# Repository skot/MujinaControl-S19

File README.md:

# MujinaControl-S19

An open-hardware Antminer S19 controlboard built around the Rockchip RV1106G2, for [Mujina](https://mujina.org) mining firmware. It keeps the bitcrane v3.1 form factor, outline, mounting holes and miner connectors, and replaces bitcrane's RP2040 with a Linux-capable SoC, Ethernet and local storage.

**Status (2026-11-12):** schematic complete, PCB placed and fully routed on six layers. ERC 0; DRC 0 violations, 0 unconnected items, 0 schematic-parity issues. Every purchased part has a fab (LCSC) part number. **Not yet reviewed for manufacturing and not built or tested.** Do not order until the review below is done.

Open `MujinaControl-S19.kicad_pro` with **KiCad 10.99 or later**. The files use a newer format than KiCad 10.0 can read.

## Hardware

- **SoC:** RV1106G2 with 128 MB in-package DDR3L, 24 MHz crystal and RTC crystal.
- **Storage:** W25N02KVZEIR 2 Gbit (256 MB) SPI NAND on the quad-SPI bus, following the Luckfox Pico Pro/Max, plus a microSD socket. A bootable NAND takes precedence over microSD.
- **Network and USB:** 100BASE-TX through the SoC's internal PHY and an integrated MagJack. USB-C device port for recovery and console; VBUS is detection-only, so **12 V must be present for USB recovery**.
- **Power:** 12 V from J1's 6-pin input (pins 1–3 positive, 4–6 ground) through reverse-polarity P-MOSFET Q1 (NTTFS008P03P8Z) and an SMBJ15A TVS. There is no controller fuse. Six TPS62933 bucks: 12 V → 5 V system (2 A budget), then sequenced 0.9 V core, 0.9 V CPU, 1.35 V DDR, 1.8 V and 3.3 V. Five TPS3808 supervisors (trip at about 90 % of each rail) qualify the sequence and hold reset.
- **Hashboards:** three ports, each with its own hardware UART, sharing one hashboard I²C bus; BCB100-style I²C/UART pull-ups and plug-detect pull-downs, and a TPS22919 switched 3.3 V supply per port, enabled directly by SoC GPIOs.
- **Fans:** four independent channels, PWM and tach, each sized for 3 A; the input stage carries all four fans plus the board. Each channel has both a 1×4 2.54 mm and a 2×2 4.2 mm footprint; fit one. Two 100 µF bulk capacitors on the fan rail.
- **PSU and accessories:** PSU I²C and enable, accessory header J15 (display I²C, GPIO, 5 V / 3.3 V), console UART on J16 (pin 1 TX, 2 GND, 3 RX, 3.3 V), RESET and BOOT (maskrom) right-angle buttons beside the Ethernet jack.

J1–J14 keep bitcrane's pin assignments. The SoC pin allocation is in `docs/pin-allocation.md`.

## Schematic

Ten sheets: system overview, SoC interfaces, sequenced regulators, power qualification, SoC supply and bypass, boot storage and clocks, Ethernet and USB, hashboard interfaces, fan interfaces, input power and service. Cross-sheet signals use global labels; resistors use US-style symbols.

## PCB

- 110 × 100 mm, six layers, nominal 1.6 mm FR-4, ENIG, 1 oz outer / 0.5 oz inner, using the fab's JLC06161H-3313 stackup (`docs/pcb-stackup.md`).
- Layers: F.Cu signals and parts; In1 ground; In2 3.3 V plane with islands for core, DDR, 1.8 V, 5 V and 12 V; In3 slow signals; In4 ground; B.Cu signals.
- 310 footprints, 1925 tracks, 774 vias. All vias are 0.45 mm diameter / 0.30 mm drill; minimum track 0.127 mm (SoC escapes and Ethernet pairs).
- USB, Ethernet, SD card and SPI NAND are length-matched within the RV1106 hardware-guide limits.
- Each regulator follows the TPS62933 datasheet layout, with its own stitched ground pour. 414 ground vias in total; wherever a via is allowed, no point is more than 6 mm from one.
- Reference designators are hidden on the silkscreen; the printed artwork is the RESET and BOOT labels and the Mujina badger logo.

Routing details, measurements and history are in `docs/routing-current.md`. The other routing documents describe the board before the 2026-11-10 rip-up.

## Assembly and parts

The board is meant to be assembled by the fab. Every purchased part carries `LCSC` and `MPN` fields: 65 part numbers, 24 basic, 9 preferred and 32 extended, checked against live stock on 2026-11-12. The RV1106G2 needs the fab's standard (not economic) assembly. Stock was low for Q1 and the hashboard connectors J3–J5. See `docs/bom-fab-stock.md`. Fab settings are in `MujinaControl-S19.fab.json` (`order: false`).

## Before ordering

1. **Manufacturing review.** The routing was largely laid by a grid search: it is rule-clean but not tidy. The east-side hashboard lines are long (up to 117 mm) with up to 9 vias. They are slow signals, but they should be reviewed and could be shortened.
2. **Hashboard and PSU compatibility.** Confirm the real S19 hashboard and PSU voltages, reset and plug-detect polarity, PSU-enable polarity and powered/unpowered behaviour. Matching bitcrane's connections is not a measured compatibility test.
3. **Power.** Check cold start, slow ramp, brownout and shutdown on all rails, the supervisor thresholds, and regulator transient response. Measure Q1 and the 12 V copper at the full four-fan load. Upstream wiring must protect against shorts, as there is no controller fuse.
4. **Footprints and parts.** Audit the footprints against datasheets, especially the SoC and NAND exposed pads, MagJack, crystals, inductors and microSD. Re-check stock before ordering.
5. **Firmware.** Bring up the UART, PWM and I²C pin groups, fan tach, hashboard power GPIOs, NAND boot and USB recovery in the BSP. Keep the CPU at its fixed 0.9 V operating point.
6. **On hardware.** Tune the crystals; check USB and Ethernet signal integrity, ESD, thermals and EMC.

## Files

- `MujinaControl-S19.kicad_pro` with ten `.kicad_sch` sheets, `.kicad_pcb` and `.kicad_dru` (custom rules).
- `lib/`, `models/`, `3d/`: project-local symbols, footprints and 3D models.
- `docs/`: design notes for each change (stackup, placement, regulators, routing, parts).
- `scripts/`: the original generator `build_schematic.py`. **Do not rerun it**; it would overwrite the hand-edited schematic. `validate_design.py` and `verify_readability.py` are read-only checks.
- Check reports, renders and working evidence are kept outside this repository, in `build/MujinaControl-S19/` at the workspace root.

## Sources and attribution

- [Braiins BCB100](https://github.com/braiins/BCB100): open-source S19 control board (CERN-OHL-S v2), used as the reference for hashboard interface biasing and logic-power control (I2C/UART pull-ups, plug-detect pull-downs and per-port switched 3.3 V). Thanks to Braiins for publishing it.
- [bitcrane](https://github.com/skot/bitcrane) v3.1 (CERN-OHL v2): form factor, outline, mounting holes, connector pinouts and placements, fan-header options, and the inherited `bitaxe` and `bitcrane` libraries.
- Raven1106 v1.1: starting RV1106 package-pin definition, QFN footprint and model, and storage reference. Its full SBC circuit was not copied. No top-level licence was found for Raven; clarify reuse terms for the derived library assets before publishing them more widely.
- Luckfox Pico Pro/Max: SPI NAND reference.
- Rockchip RV1106 datasheet Rev 2.2 and hardware design guide: pin functions, power and layout rules.
- [TI TPS62933](https://www.ti.com/lit/ds/symlink/tps62933.pdf), [TI TPS3808](https://www.ti.com/lit/ds/symlink/tps3808.pdf), [TI TPS22919](https://www.ti.com/lit/ds/symlink/tps22919.pdf), [onsemi NTTFS008P03P8Z](https://www.onsemi.com/download/data-sheet/pdf/nttfs008p03p8z-d.pdf) and [Nexperia PESD3V3Y1BSF](https://assets.nexperia.com/documents/data-sheet/PESD3V3Y1BSF.pdf) datasheets.

Standard KiCad symbols and footprints are copied into the project-local libraries. Their original licence and attribution markings still apply.

## License

CERN Open Hardware Licence v2, Strongly Reciprocal (`LICENSE`).

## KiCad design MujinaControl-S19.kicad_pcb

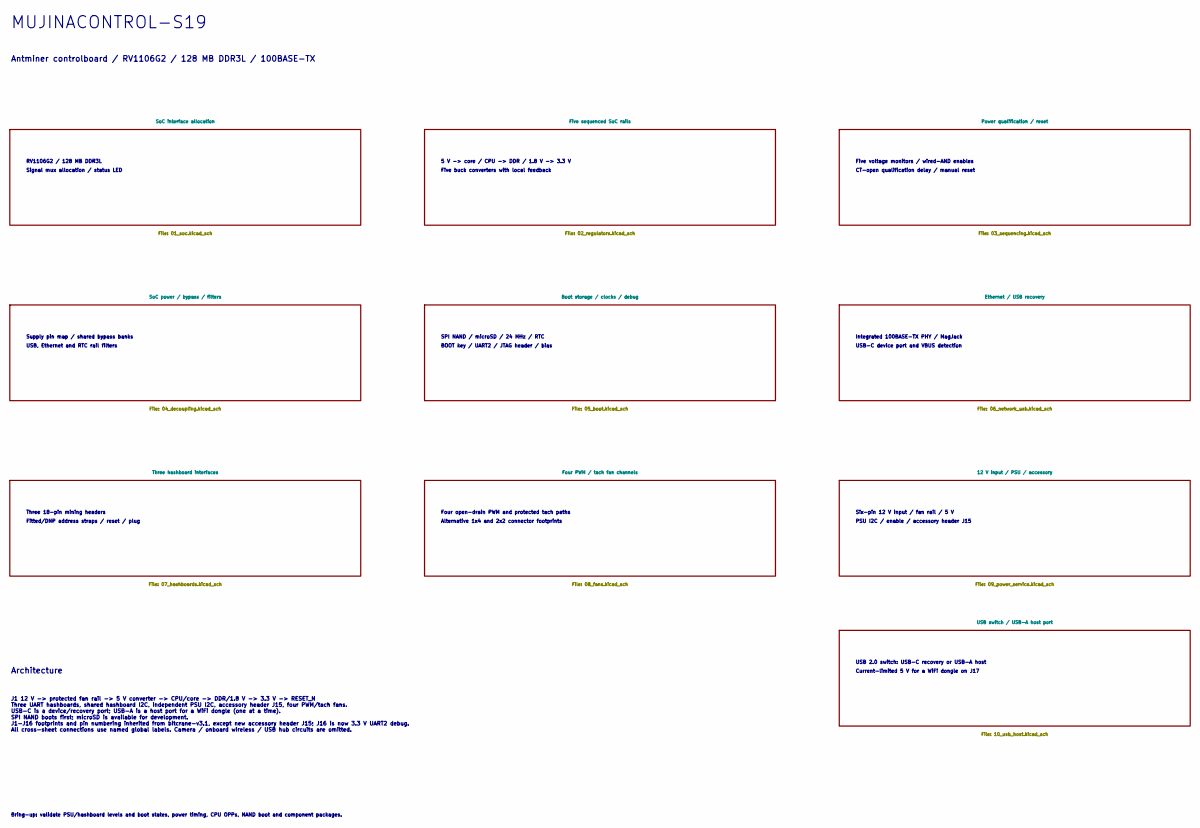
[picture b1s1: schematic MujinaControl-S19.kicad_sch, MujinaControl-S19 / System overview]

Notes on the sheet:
USB, Ethernet and RTC rail filters
Integrated 100BASE-TX PHY / MagJack
Five voltage monitors / wired-AND enables
PSU I2C / enable / accessory header J15
USB 2.0 switch: USB-C recovery or USB-A host
MUJINACONTROL-S19
5 V -> core / CPU -> DDR / 1.8 V -> 3.3 V
Architecture
Five buck converters with local feedback
BOOT key / UART2 / JTAG header / bias
Alternative 1x4 and 2x2 connector footprints
USB-C device port and VBUS detection
SPI NAND / microSD / 24 MHz / RTC
J1 12 V -> protected fan rail -> 5 V converter -> CPU/core -> DDR/1.8 V -> 3.3 V -> RESET_N Three UART hashboards, shared hashboard I2C, independent PSU I2C, accessory header J15, four PWM/tach fans. USB-C is a device/recovery port; USB-A is a host port for a WiFi dongle (one at a time).
SPI NAND boots first; microSD is available for development. J1-J16 footprints and pin numbering inherited from bitcrane-v3.1, except new accessory header J15; J16 is now 3.3 V UART2 debug. All cross-sheet connections use named global labels. Camera / onboard wireless / USB hub circuits are omitted.
Supply pin map / shared bypass banks
Antminer controlboard / RV1106G2 / 128 MB DDR3L / 100BASE-TX
CT-open qualification delay / manual reset
Fitted/DNP address straps / reset / plug
RV1106G2 / 128 MB DDR3L
Current-limited 5 V for a WiFi dongle on J17
Bring-up: validate PSU/hashboard levels and boot states, power timing, CPU OPPs, NAND boot and component packages.
Signal mux allocation / status LED
Three 18-pin mining headers
Four open-drain PWM and protected tach paths
Six-pin 12 V input / fan rail / 5 V

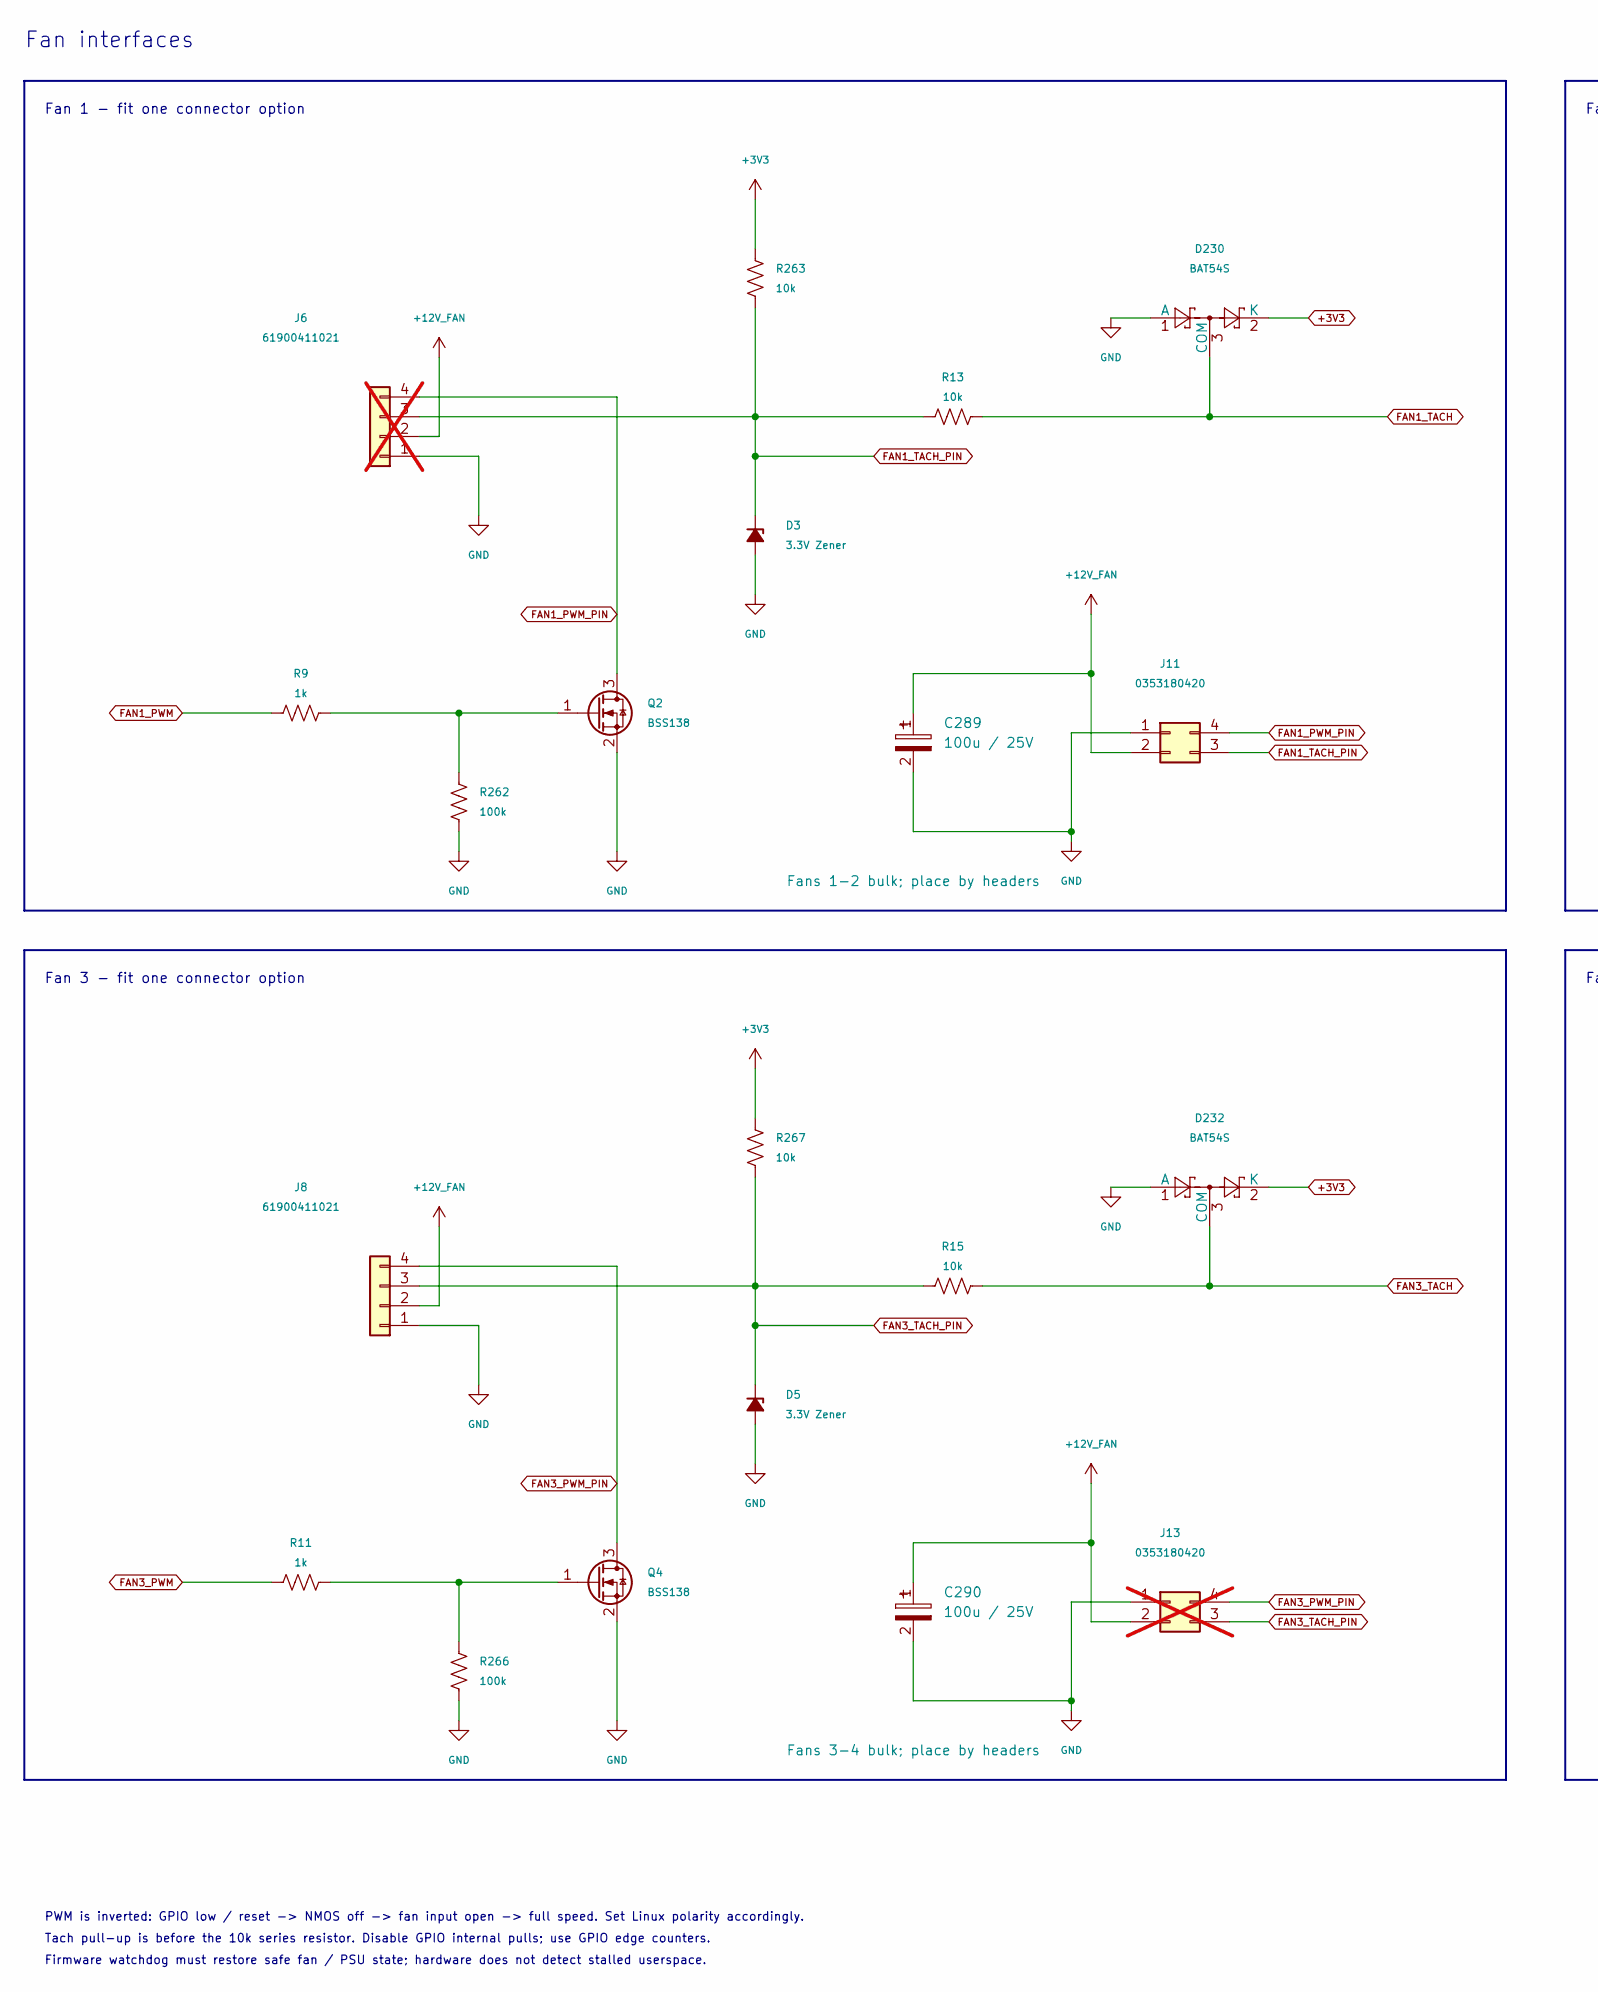
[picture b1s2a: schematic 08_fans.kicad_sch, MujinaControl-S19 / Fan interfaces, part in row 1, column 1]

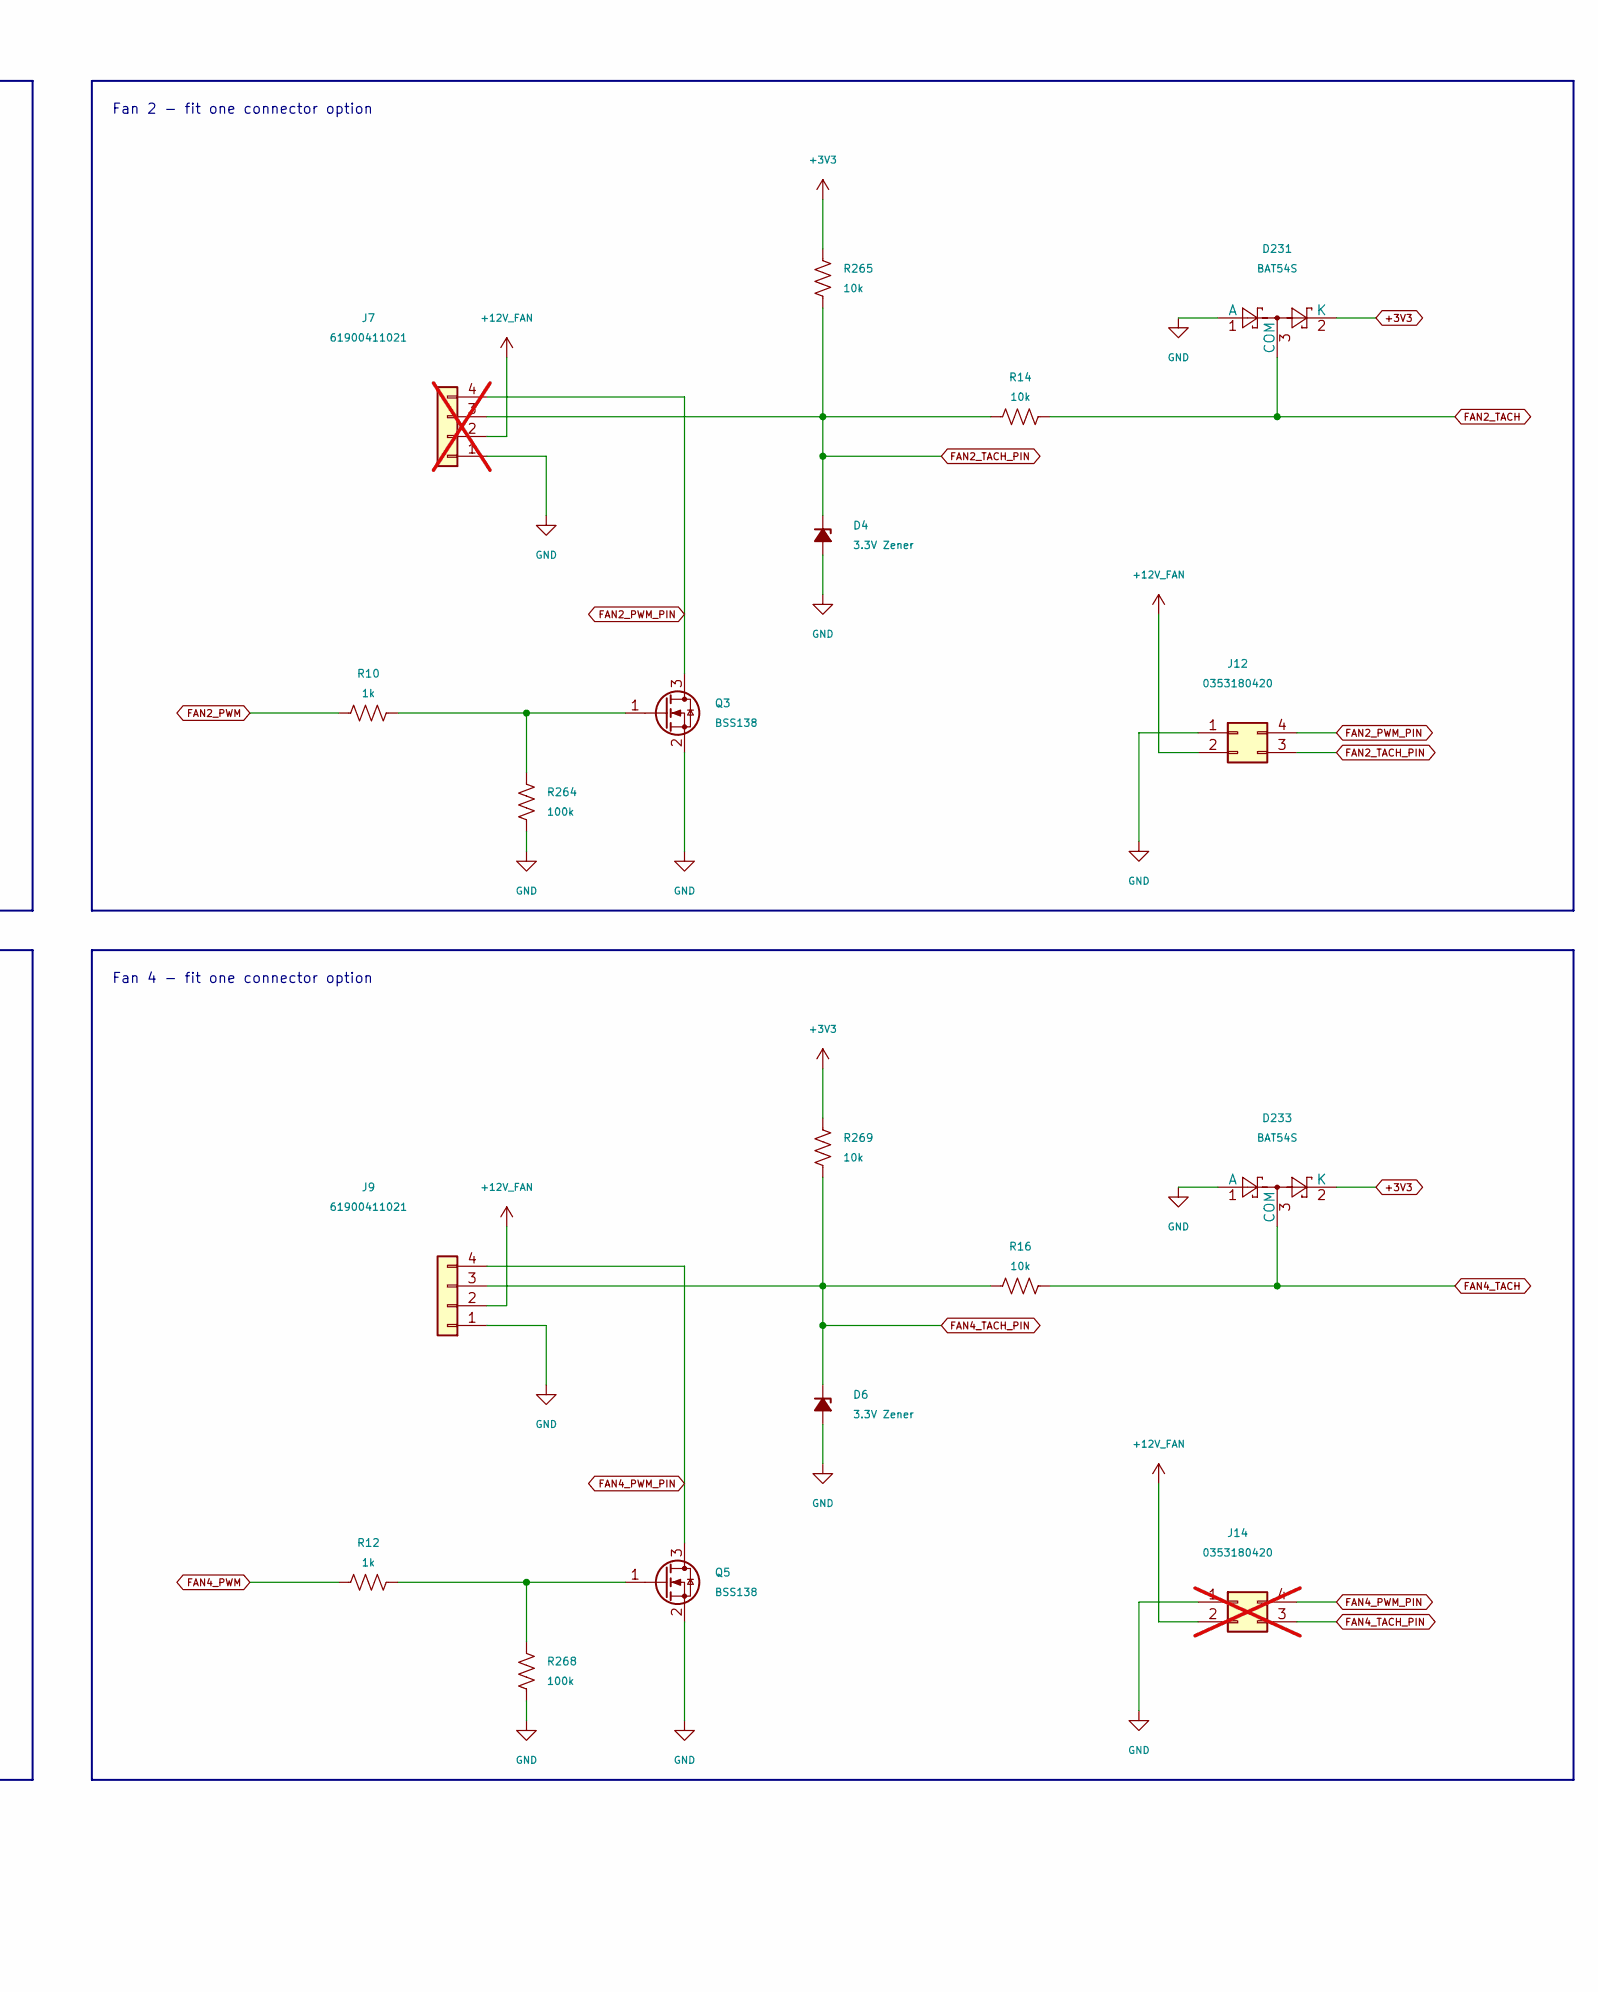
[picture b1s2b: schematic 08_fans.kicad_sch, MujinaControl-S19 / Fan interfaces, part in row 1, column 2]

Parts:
C289, C290: 100u / 25V; CP_Elec_6.3x7.7; MPN EEHZC1E101XP; LCSC C178640
D3, D4, D5, D6: 3.3V Zener; D_SOD-123; MPN BZT52C3V3; LCSC C19077396
D230, D231, D232, D233: BAT54S; SOT-23; MPN BAT54S; LCSC C7420333
J6, J7: 61900411021; CONN-TH_4P-P2.54_HCTL_HC-2510-4AW; MPN HC-2510-4AW; LCSC C2982043; not fitted
J8, J9: 61900411021; CONN-TH_4P-P2.54_HCTL_HC-2510-4AW; MPN HC-2510-4AW; LCSC C2982043
J11, J12: 0353180420; CONN-TH_4P-P4.20_5557-2X2AW; MPN 4.2-2*2AW; LCSC C54909
J13, J14: 0353180420; CONN-TH_4P-P4.20_5557-2X2AW; MPN 4.2-2*2AW; LCSC C54909; not fitted
Q2, Q3, Q4, Q5: BSS138; SOT-23; MPN BSS138; LCSC C7420339
R9, R10, R11, R12: 1k; R_0402_1005Metric; MPN 0402WGF1001TCE; LCSC C11702
R13, R14, R15, R16, R263, R265, R267, R269: 10k; R_0402_1005Metric; MPN 0402WGF1002TCE; LCSC C25744
R262, R264, R266, R268: 100k; R_0402_1005Metric; MPN 0402WGF1003TCE; LCSC C25741

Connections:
+3V3: D230.2 (K), D231.2 (K), D232.2 (K), D233.2 (K), R263.1, R265.1, R267.1, R269.1; also elsewhere on the board
+12V_FAN: C289.1, C290.1, J6.2, J7.2, J8.2, J9.2, J11.2, J12.2, J13.2, J14.2; also elsewhere on the board
FAN1_PWM: R9.1; also elsewhere on the board
FAN1_PWM_PIN: J6.4, J11.4, Q2.3 (D)
FAN1_TACH: D230.3 (COM), R13.2; also elsewhere on the board
FAN1_TACH_PIN: D3.1 (K), J6.3, J11.3, R13.1, R263.2
FAN2_PWM: R10.1; also elsewhere on the board
FAN2_PWM_PIN: J7.4, J12.4, Q3.3 (D)
FAN2_TACH: D231.3 (COM), R14.2; also elsewhere on the board
FAN2_TACH_PIN: D4.1 (K), J7.3, J12.3, R14.1, R265.2
FAN3_PWM: R11.1; also elsewhere on the board
FAN3_PWM_PIN: J8.4, J13.4, Q4.3 (D)
FAN3_TACH: D232.3 (COM), R15.2; also elsewhere on the board
FAN3_TACH_PIN: D5.1 (K), J8.3, J13.3, R15.1, R267.2
FAN4_PWM: R12.1; also elsewhere on the board
FAN4_PWM_PIN: J9.4, J14.4, Q5.3 (D)
FAN4_TACH: D233.3 (COM), R16.2; also elsewhere on the board
FAN4_TACH_PIN: D6.1 (K), J9.3, J14.3, R16.1, R269.2
GND: C289.2, C290.2, D3.2 (A), D4.2 (A), D5.2 (A), D6.2 (A), D230.1 (A), D231.1 (A), D232.1 (A), D233.1 (A), J6.1, J7.1, J8.1, J9.1, J11.1, J12.1, J13.1, J14.1, Q2.2 (S), Q3.2 (S), Q4.2 (S), Q5.2 (S), R262.2, R264.2, R266.2, R268.2; also elsewhere on the board
unnamed: Q2.1 (G), R9.2, R262.1
unnamed: Q3.1 (G), R10.2, R264.1
unnamed: Q4.1 (G), R11.2, R266.1
unnamed: Q5.1 (G), R12.2, R268.1

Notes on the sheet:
Fan 4 - fit one connector option
Tach pull-up is before the 10k series resistor. Disable GPIO internal pulls; use GPIO edge counters.
Firmware watchdog must restore safe fan / PSU state; hardware does not detect stalled userspace.
Fan interfaces
PWM is inverted: GPIO low / reset -> NMOS off -> fan input open -> full speed. Set Linux polarity accordingly.
Fan 2 - fit one connector option
Fan 1 - fit one connector option
Fan 3 - fit one connector option

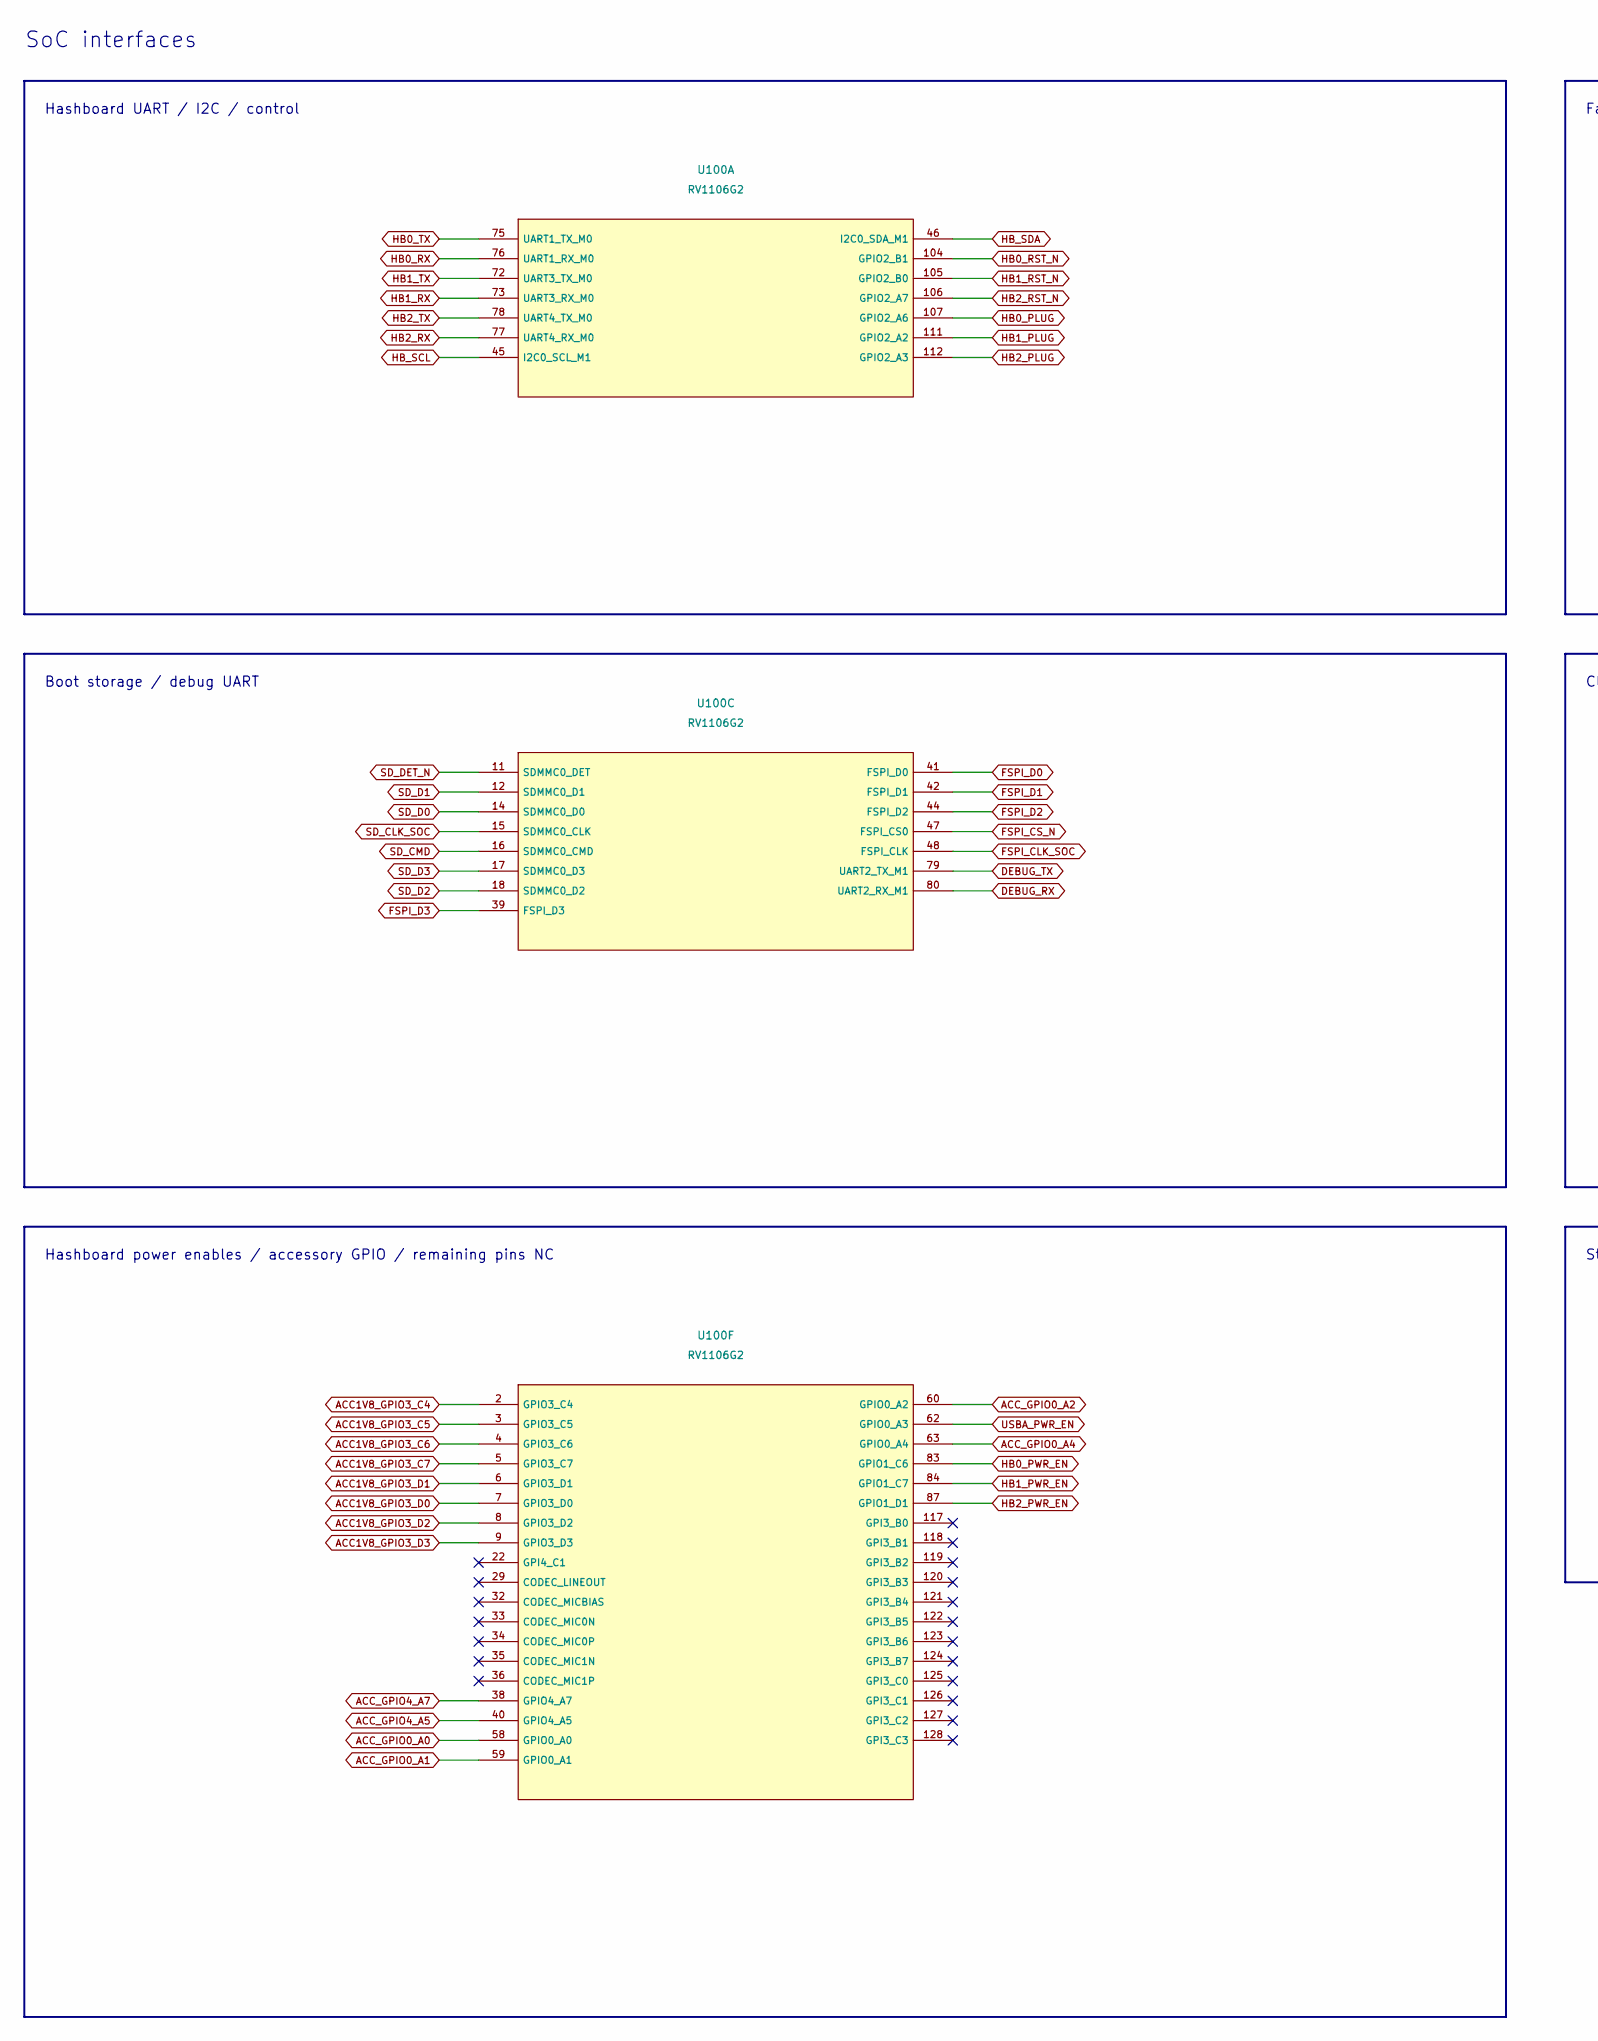
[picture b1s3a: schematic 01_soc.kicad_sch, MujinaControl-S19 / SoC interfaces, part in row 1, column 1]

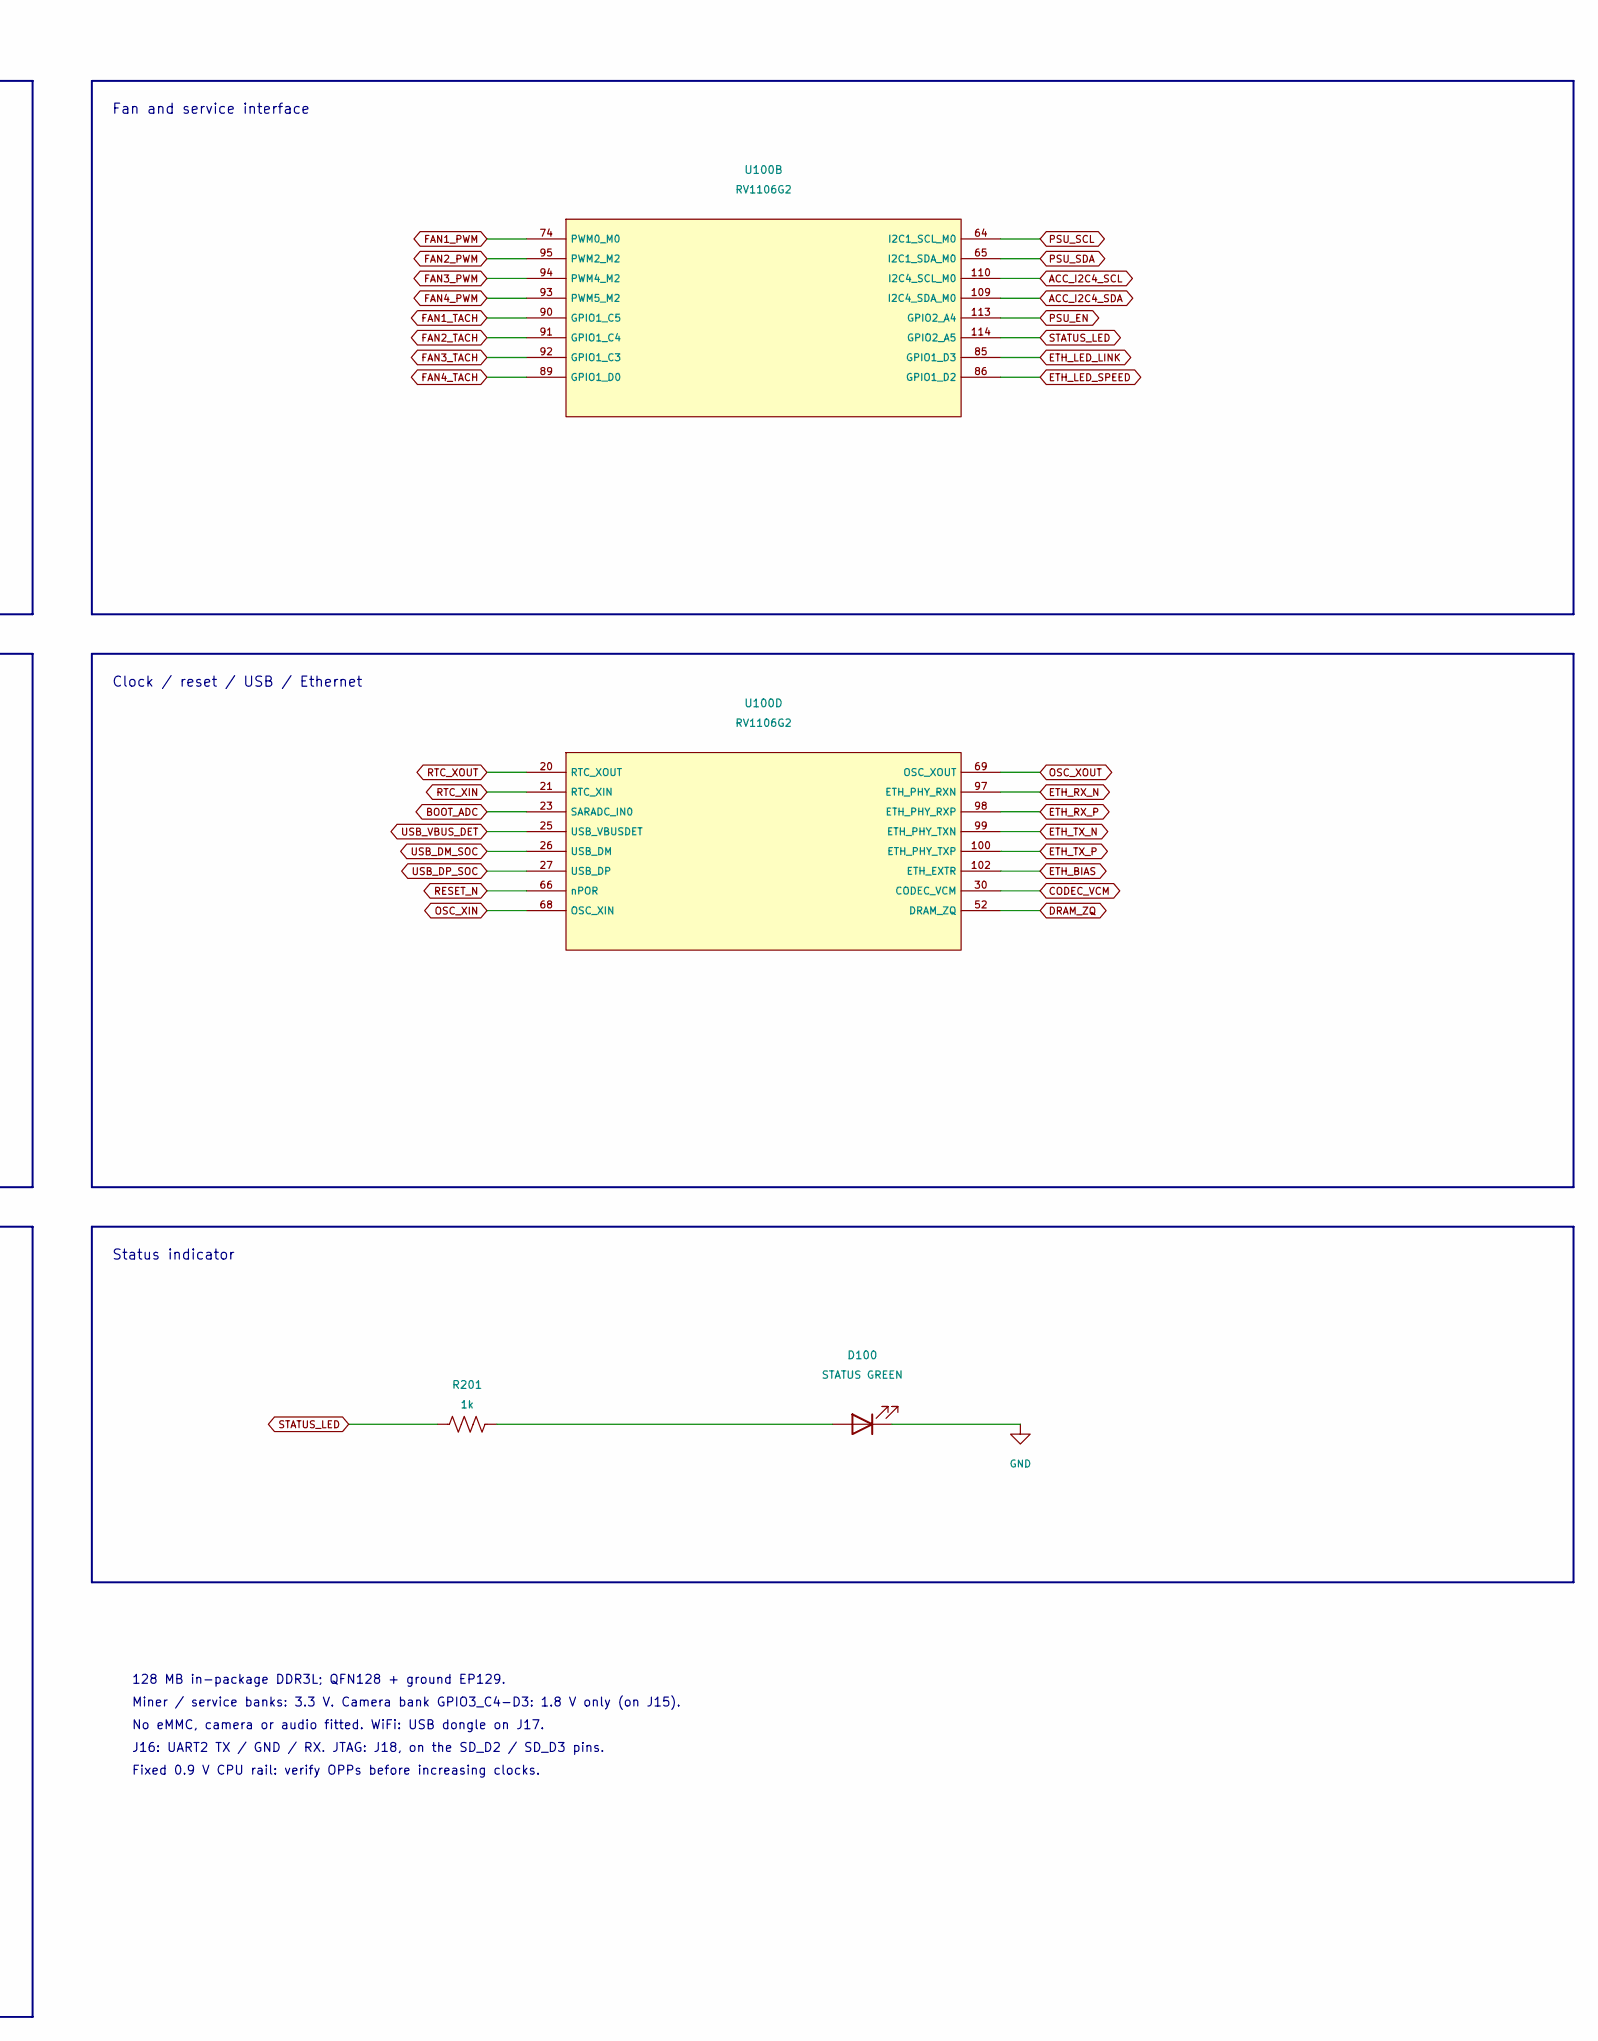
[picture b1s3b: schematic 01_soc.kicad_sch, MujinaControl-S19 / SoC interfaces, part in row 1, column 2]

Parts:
D100: STATUS GREEN; LED_0603_1608Metric; MPN LTST-C190KGKT; LCSC C125094
R201: 1k; R_0402_1005Metric; MPN 0402WGF1001TCE; LCSC C11702
U100: RV1106G2; Rockchip_QFN-128-1EP_12.3x12.3mm_P0.35mm_EP7x7mm; MPN RV1106G2; LCSC C5272606

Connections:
ACC1V8_GPIO3_C4: U100.2 (GPIO3_C4); also elsewhere on the board
ACC1V8_GPIO3_C5: U100.3 (GPIO3_C5); also elsewhere on the board
ACC1V8_GPIO3_C6: U100.4 (GPIO3_C6); also elsewhere on the board
ACC1V8_GPIO3_C7: U100.5 (GPIO3_C7); also elsewhere on the board
ACC1V8_GPIO3_D0: U100.7 (GPIO3_D0); also elsewhere on the board
ACC1V8_GPIO3_D1: U100.6 (GPIO3_D1); also elsewhere on the board
ACC1V8_GPIO3_D2: U100.8 (GPIO3_D2); also elsewhere on the board
ACC1V8_GPIO3_D3: U100.9 (GPIO3_D3); also elsewhere on the board
ACC_GPIO0_A0: U100.58 (GPIO0_A0); also elsewhere on the board
ACC_GPIO0_A1: U100.59 (GPIO0_A1); also elsewhere on the board
ACC_GPIO0_A2: U100.60 (GPIO0_A2); also elsewhere on the board
ACC_GPIO0_A4: U100.63 (GPIO0_A4); also elsewhere on the board
ACC_GPIO4_A5: U100.40 (GPIO4_A5); also elsewhere on the board
ACC_GPIO4_A7: U100.38 (GPIO4_A7); also elsewhere on the board
ACC_I2C4_SCL: U100.110 (I2C4_SCL_M0); also elsewhere on the board
ACC_I2C4_SDA: U100.109 (I2C4_SDA_M0); also elsewhere on the board
BOOT_ADC: U100.23 (SARADC_IN0); also elsewhere on the board
CODEC_VCM: U100.30 (CODEC_VCM); also elsewhere on the board
DEBUG_RX: U100.80 (UART2_RX_M1); also elsewhere on the board
DEBUG_TX: U100.79 (UART2_TX_M1); also elsewhere on the board
DRAM_ZQ: U100.52 (DRAM_ZQ); also elsewhere on the board
ETH_BIAS: U100.102 (ETH_EXTR); also elsewhere on the board
ETH_LED_LINK: U100.85 (GPIO1_D3); also elsewhere on the board
ETH_LED_SPEED: U100.86 (GPIO1_D2); also elsewhere on the board
ETH_RX_N: U100.97 (ETH_PHY_RXN); also elsewhere on the board
ETH_RX_P: U100.98 (ETH_PHY_RXP); also elsewhere on the board
ETH_TX_N: U100.99 (ETH_PHY_TXN); also elsewhere on the board
ETH_TX_P: U100.100 (ETH_PHY_TXP); also elsewhere on the board
FAN1_PWM: U100.74 (PWM0_M0); also elsewhere on the board
FAN1_TACH: U100.90 (GPIO1_C5); also elsewhere on the board
FAN2_PWM: U100.95 (PWM2_M2); also elsewhere on the board
FAN2_TACH: U100.91 (GPIO1_C4); also elsewhere on the board
FAN3_PWM: U100.94 (PWM4_M2); also elsewhere on the board
FAN3_TACH: U100.92 (GPIO1_C3); also elsewhere on the board
FAN4_PWM: U100.93 (PWM5_M2); also elsewhere on the board
FAN4_TACH: U100.89 (GPIO1_D0); also elsewhere on the board
FSPI_CLK_SOC: U100.48 (FSPI_CLK); also elsewhere on the board
FSPI_CS_N: U100.47 (FSPI_CS0); also elsewhere on the board
FSPI_D0: U100.41 (FSPI_D0); also elsewhere on the board
FSPI_D1: U100.42 (FSPI_D1); also elsewhere on the board
FSPI_D2: U100.44 (FSPI_D2); also elsewhere on the board
FSPI_D3: U100.39 (FSPI_D3); also elsewhere on the board
GND: D100.1 (K); also elsewhere on the board
HB0_PLUG: U100.107 (GPIO2_A6); also elsewhere on the board
HB0_PWR_EN: U100.83 (GPIO1_C6); also elsewhere on the board
HB0_RST_N: U100.104 (GPIO2_B1); also elsewhere on the board
HB0_RX: U100.76 (UART1_RX_M0); also elsewhere on the board
HB0_TX: U100.75 (UART1_TX_M0); also elsewhere on the board
HB1_PLUG: U100.111 (GPIO2_A2); also elsewhere on the board
HB1_PWR_EN: U100.84 (GPIO1_C7); also elsewhere on the board
HB1_RST_N: U100.105 (GPIO2_B0); also elsewhere on the board
HB1_RX: U100.73 (UART3_RX_M0); also elsewhere on the board
HB1_TX: U100.72 (UART3_TX_M0); also elsewhere on the board
HB2_PLUG: U100.112 (GPIO2_A3); also elsewhere on the board
HB2_PWR_EN: U100.87 (GPIO1_D1); also elsewhere on the board
HB2_RST_N: U100.106 (GPIO2_A7); also elsewhere on the board
HB2_RX: U100.77 (UART4_RX_M0); also elsewhere on the board
HB2_TX: U100.78 (UART4_TX_M0); also elsewhere on the board
HB_SCL: U100.45 (I2C0_SCL_M1); also elsewhere on the board
HB_SDA: U100.46 (I2C0_SDA_M1); also elsewhere on the board
unnamed: D100.2 (A), R201.2
OSC_XIN: U100.68 (OSC_XIN); also elsewhere on the board
OSC_XOUT: U100.69 (OSC_XOUT); also elsewhere on the board
PSU_EN: U100.113 (GPIO2_A4); also elsewhere on the board
PSU_SCL: U100.64 (I2C1_SCL_M0); also elsewhere on the board
PSU_SDA: U100.65 (I2C1_SDA_M0); also elsewhere on the board
RESET_N: U100.66 (nPOR); also elsewhere on the board
RTC_XIN: U100.21 (RTC_XIN); also elsewhere on the board
RTC_XOUT: U100.20 (RTC_XOUT); also elsewhere on the board
SD_CLK_SOC: U100.15 (SDMMC0_CLK); also elsewhere on the board
SD_CMD: U100.16 (SDMMC0_CMD); also elsewhere on the board
SD_D0: U100.14 (SDMMC0_D0); also elsewhere on the board
SD_D1: U100.12 (SDMMC0_D1); also elsewhere on the board
SD_D2: U100.18 (SDMMC0_D2); also elsewhere on the board
SD_D3: U100.17 (SDMMC0_D3); also elsewhere on the board
SD_DET_N: U100.11 (SDMMC0_DET); also elsewhere on the board
STATUS_LED: R201.1, U100.114 (GPIO2_A5)
USBA_PWR_EN: U100.62 (GPIO0_A3); also elsewhere on the board
USB_DM_SOC: U100.26 (USB_DM); also elsewhere on the board
USB_DP_SOC: U100.27 (USB_DP); also elsewhere on the board
USB_VBUS_DET: U100.25 (USB_VBUSDET); also elsewhere on the board

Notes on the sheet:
Clock / reset / USB / Ethernet
Status indicator
Fixed 0.9 V CPU rail: verify OPPs before increasing clocks.
Miner / service banks: 3.3 V. Camera bank GPIO3_C4-D3: 1.8 V only (on J15).
Hashboard UART / I2C / control
No eMMC, camera or audio fitted. WiFi: USB dongle on J17.
Boot storage / debug UART
Hashboard power enables / accessory GPIO / remaining pins NC
J16: UART2 TX / GND / RX. JTAG: J18, on the SD_D2 / SD_D3 pins.
Fan and service interface
128 MB in-package DDR3L; QFN128 + ground EP129.
SoC interfaces
